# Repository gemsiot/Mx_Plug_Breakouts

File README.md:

# Mx_Plug_Breakouts
Breakouts for GEMS standard M12 and M8 plug types for diagnostic purposes

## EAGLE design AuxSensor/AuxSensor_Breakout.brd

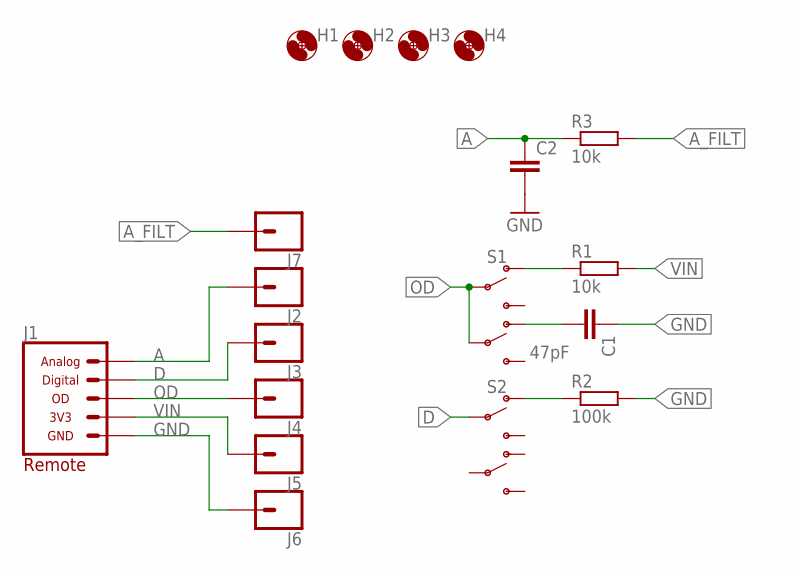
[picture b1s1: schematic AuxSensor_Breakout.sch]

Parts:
C1: 47pF; C0805
C2: C-EU0.1UFC0805; C0805
H1, H2, H3, H4: MOUNTING_HOLE4_NP; 4_40
J1: CONN_AUX_M12_REMOTE; 1X05_M12_TE_T41410
J2, J3, J4, J5, J6, J7: CONN_BANANA_SOLDER; CON_BANANA_575-4
R1, R3: 10k; R0805
R2: 100k; R0805
S1, S2: SWITCH_DPDTJS_GULLWING; JS202011SCQN

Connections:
A: C2.1, J1.4 (ANALOG), J2.P$1, R3.1
A_FILT: J7.P$1, R3.2
D: J1.5 (DIGITAL), J3.P$1, S2.2 (P1)
GND: C1.1, C2.2, J1.3 (GND), J6.P$1, R2.2
unnamed: C1.2, S1.6 (O2)
unnamed: R2.1, S2.1 (O1)
unnamed: R1.1, S1.1 (O1)
OD: J1.2 (DIGITAL_OPENDRAIN), J4.P$1, S1.2 (P1), S1.5 (P2)
VIN: J1.1 (3V3), J5.P$1, R1.2

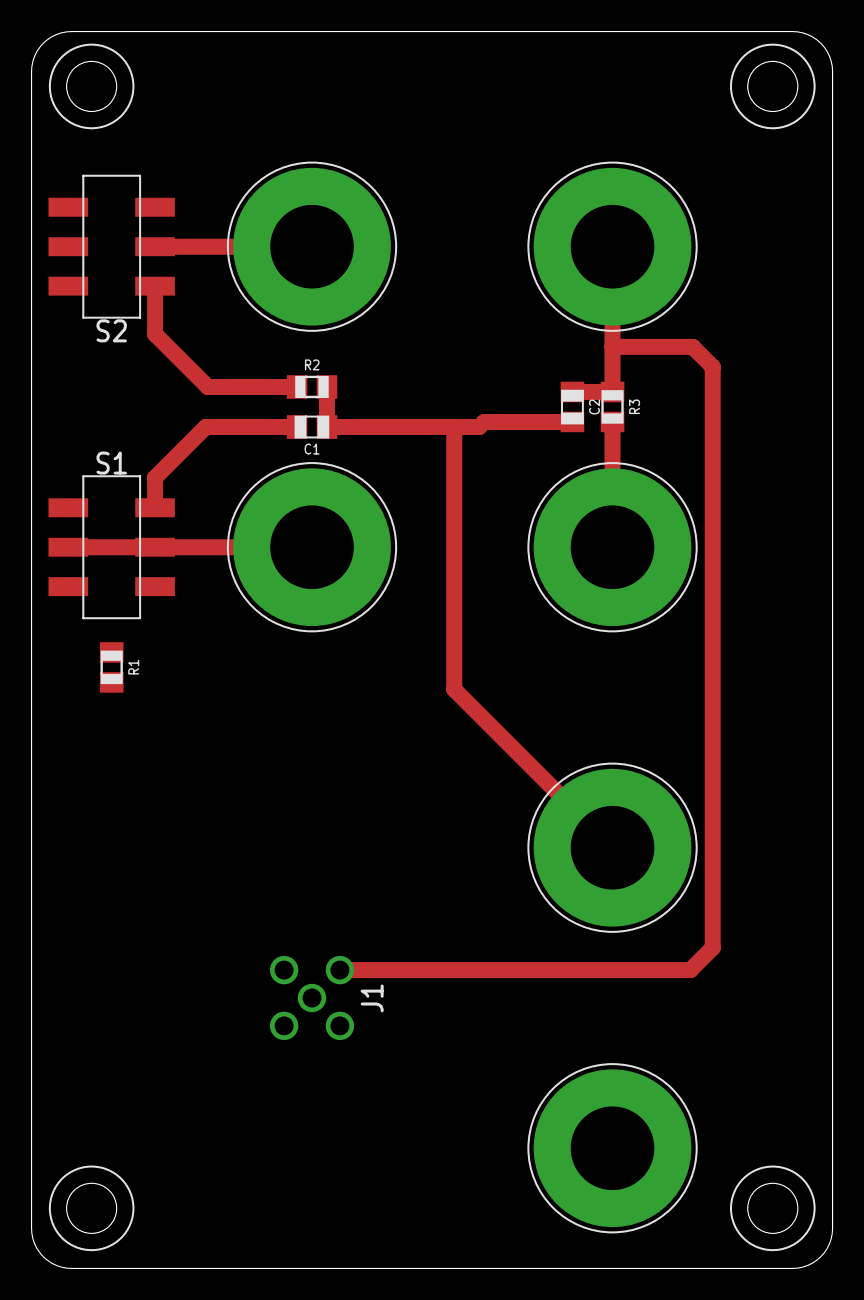
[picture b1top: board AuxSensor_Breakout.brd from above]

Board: 2 copper layers, 50.8 x 78.4 mm, 18 parts (0 on the bottom side), 9 nets.

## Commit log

2022-08-24 Added license
2024-11-02 Added Aux Sensor breakout
